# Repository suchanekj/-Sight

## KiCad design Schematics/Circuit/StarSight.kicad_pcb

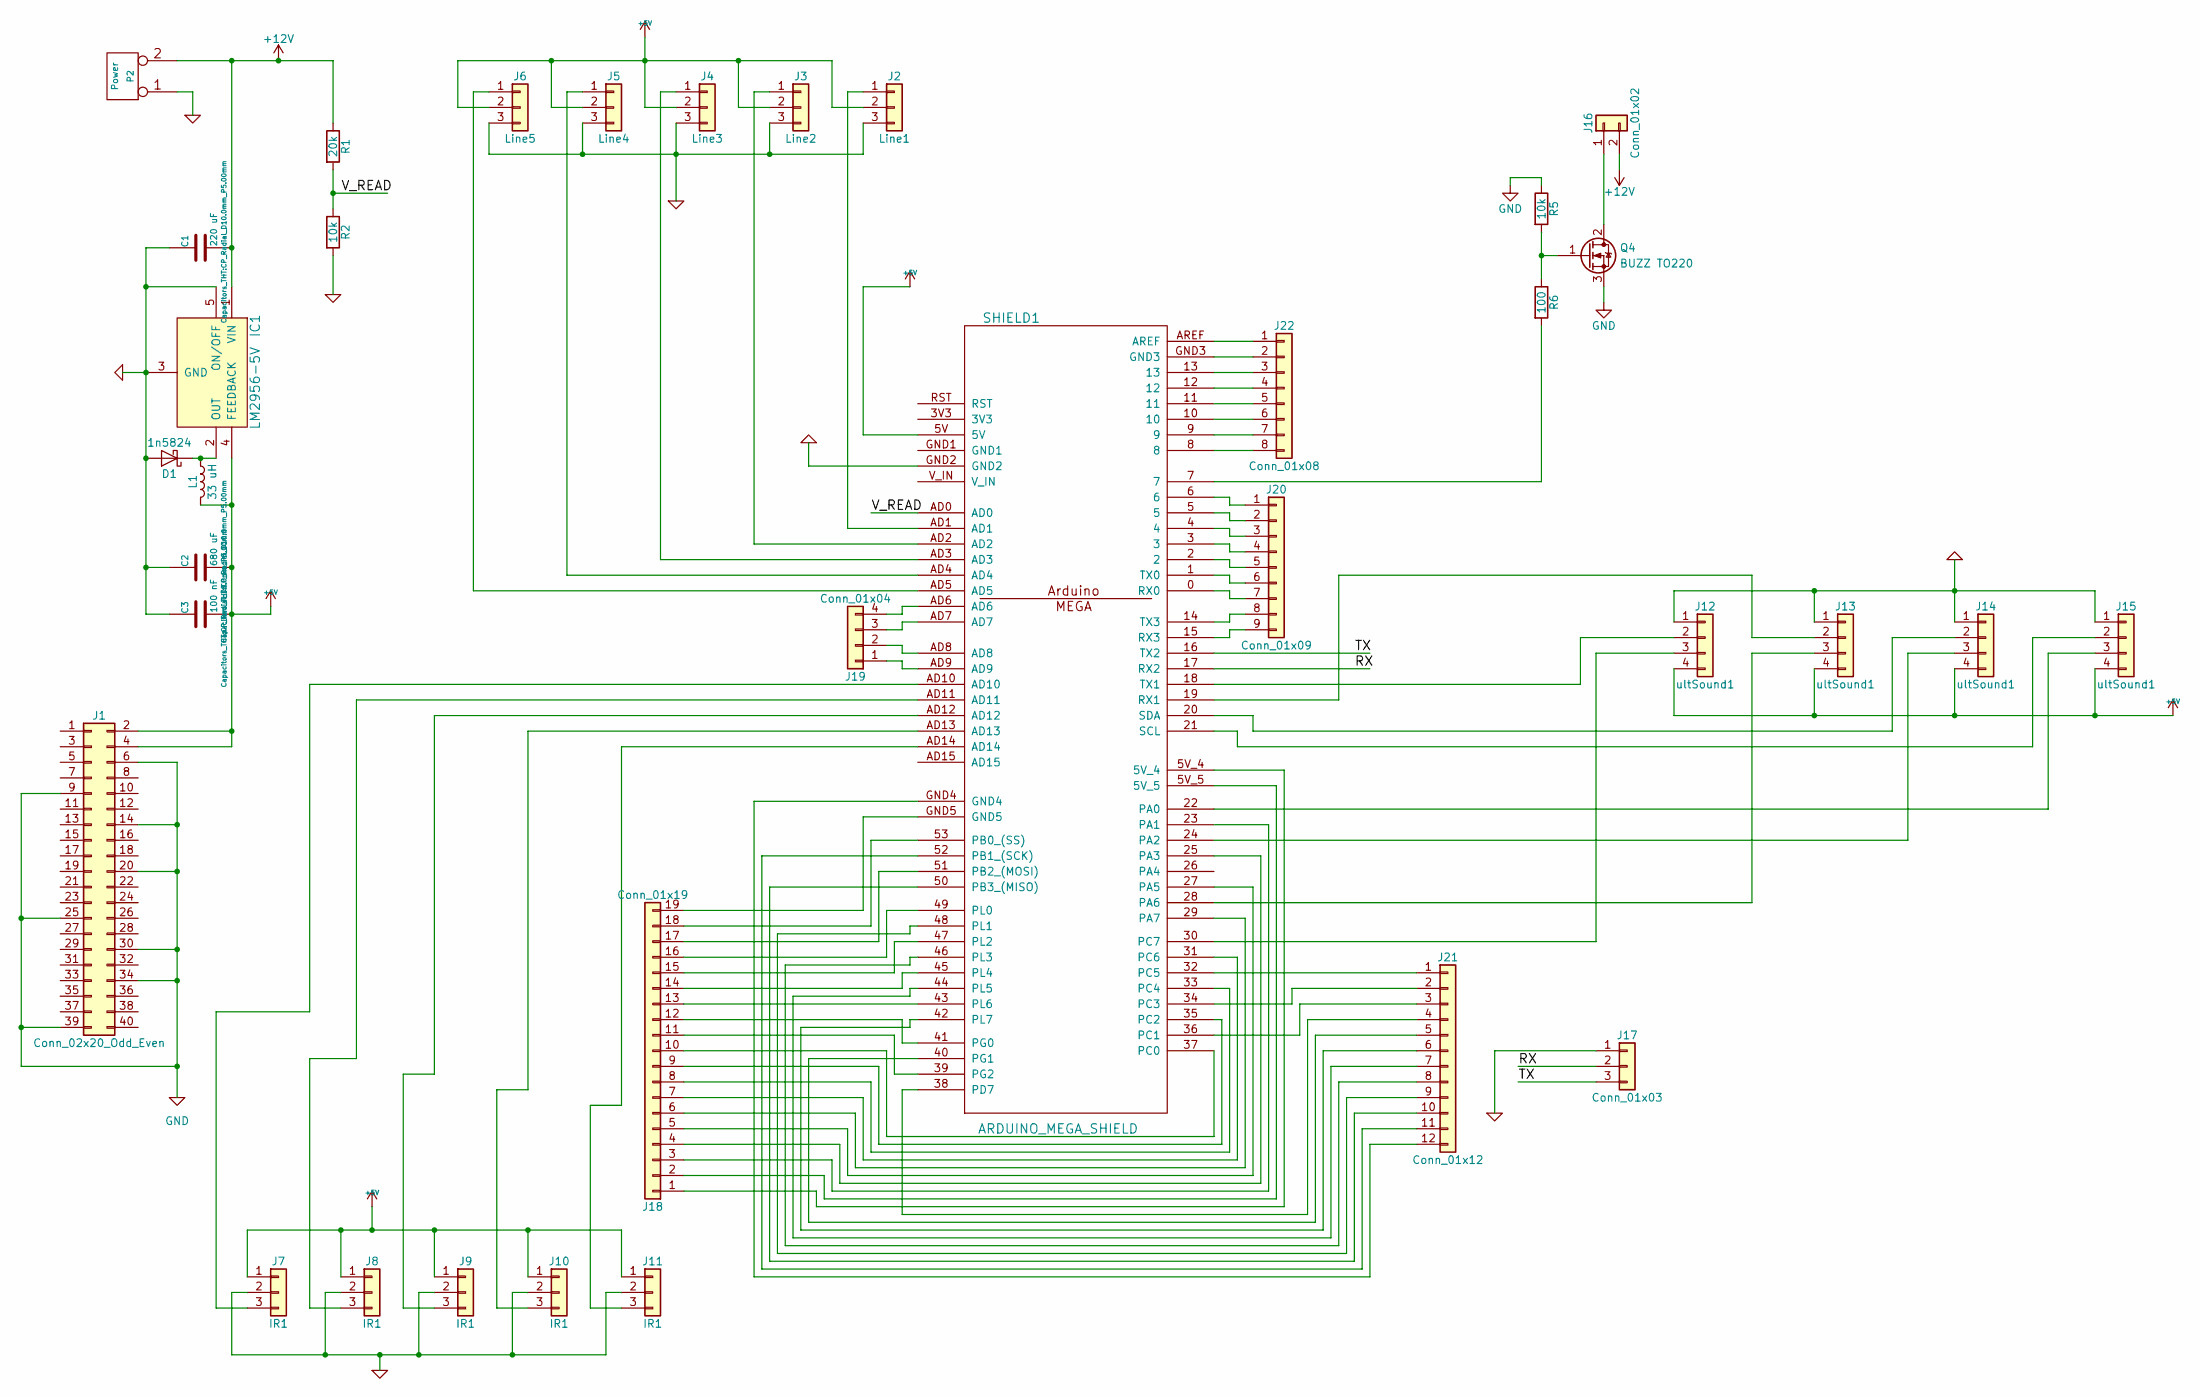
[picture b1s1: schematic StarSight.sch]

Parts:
C1: 220 uF; CP_Radial_D10.0mm_P5.00mm
C2: 680 uF; CP_Radial_D10.0mm_P5.00mm
C3: 100 nF; CP_Radial_D8.0mm_P5.00mm
D1: 1n5824; D_DO-201_P15.24mm_Horizontal
IC1: LM2956-5V; TO170P470X1016X2092-5P
J1: Conn_02x20_Odd_Even; Pin_Header_Straight_2x20_Pitch2.54mm
J2: Line1; Pin_Header_Straight_1x03_Pitch2.54mm
J3: Line2; Pin_Header_Straight_1x03_Pitch2.54mm
J4: Line3; Pin_Header_Straight_1x03_Pitch2.54mm
J5: Line4; Pin_Header_Straight_1x03_Pitch2.54mm
J6: Line5; Pin_Header_Straight_1x03_Pitch2.54mm
J7, J8, J9, J10, J11: IR1; Pin_Header_Straight_1x03_Pitch2.54mm
J12, J13, J14, J15: ultSound1; Pin_Header_Straight_1x04_Pitch2.54mm
J16: Conn_01x02; TerminalBlock_Philmore_TB132_02x5mm_Straight
J17: Conn_01x03; Pin_Header_Straight_1x03_Pitch2.54mm
J18: Conn_01x19; Pin_Header_Straight_1x19_Pitch2.54mm
J19: Conn_01x04; Pin_Header_Straight_1x04_Pitch2.54mm
J20: Conn_01x09; Pin_Header_Straight_1x09_Pitch2.54mm
J21: Conn_01x12; Pin_Header_Straight_1x12_Pitch2.54mm
J22: Conn_01x08; Pin_Header_Straight_1x08_Pitch2.54mm
L1: 33 uH; L_Toroid_Vertical_L16.0mm_W8.0mm_P7.62mm
P2: Power; TerminalBlock_Philmore_TB132_02x5mm_Straight
Q4: BUZZ TO220; Pin_Header_Straight_1x03_Pitch2.54mm
R1: 20k; R_Axial_DIN0309_L9.0mm_D3.2mm_P12.70mm_Horizontal
R2, R5: 10k; R_Axial_DIN0309_L9.0mm_D3.2mm_P12.70mm_Horizontal
R6: 100; R_Axial_DIN0309_L9.0mm_D3.2mm_P12.70mm_Horizontal
SHIELD1: ARDUINO_MEGA_SHIELD

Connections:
+5V: C2.2, C3.2, IC1.4 (FEEDBACK), J1.2, J1.4, J2.2, J3.2, J4.2, J5.2, J6.2, J7.1, J8.1, J9.1, J10.1, J11.1, J12.4, J13.4, J14.4, J15.4, L1.2, SHIELD1.5V
+12V: C1.2, IC1.1 (VIN), J16.2, P2.2 (PM), R1.1; also elsewhere on the board
/RX: J17.2, SHIELD1.17 (RX2)
/TX: J17.3, SHIELD1.16 (TX2)
/V_READ: R1.2, R2.1, SHIELD1.AD0
GND: C1.1, C2.1, C3.1, D1.2 (A), IC1.3 (GND), IC1.5 (ON/OFF), J1.6, J1.9, J1.14, J1.20, J1.25, J1.30, J1.34, J1.39, J2.3, J3.3, J4.3, J5.3, J6.3, J7.2, J8.2, J9.2, J10.2, J11.2, J12.1, J13.1, J14.1, J15.1, J17.1, P2.1, Q4.3 (S), R2.2, R5.1, SHIELD1.GND2
unnamed: D1.1 (K), IC1.2 (OUT), L1.1
unnamed 7: J16.1, Q4.2 (D); also elsewhere on the board
unnamed 8: J1.1; also elsewhere on the board
unnamed 9: J1.3; also elsewhere on the board
unnamed 10: J1.5; also elsewhere on the board
unnamed 11: J1.7; also elsewhere on the board
unnamed 12: J1.8; also elsewhere on the board
unnamed 13: J1.10; also elsewhere on the board
unnamed 14: J1.11; also elsewhere on the board
unnamed 15: J1.12; also elsewhere on the board
unnamed 16: J1.13; also elsewhere on the board
unnamed 17: J1.15; also elsewhere on the board
unnamed 18: J1.16; also elsewhere on the board
unnamed 19: J1.17; also elsewhere on the board
unnamed 20: J1.18; also elsewhere on the board
unnamed 21: J1.19; also elsewhere on the board
unnamed 22: J1.21; also elsewhere on the board
unnamed 23: J1.22; also elsewhere on the board
unnamed 24: J1.23; also elsewhere on the board
unnamed 25: J1.24; also elsewhere on the board
unnamed 26: J1.26; also elsewhere on the board
unnamed 27: J1.27; also elsewhere on the board
unnamed 28: J1.28; also elsewhere on the board
unnamed 29: J1.29; also elsewhere on the board
unnamed 30: J1.31; also elsewhere on the board
unnamed 31: J1.32; also elsewhere on the board
unnamed 32: J1.33; also elsewhere on the board
unnamed 33: J1.35; also elsewhere on the board
unnamed 34: J1.36; also elsewhere on the board
unnamed 35: J1.37; also elsewhere on the board
unnamed 36: J1.38; also elsewhere on the board
unnamed 37: J1.40; also elsewhere on the board
unnamed: J2.1, SHIELD1.AD1
unnamed: J3.1, SHIELD1.AD2
unnamed: J4.1, SHIELD1.AD3
unnamed: J5.1, SHIELD1.AD4
unnamed: J6.1, SHIELD1.AD5
unnamed: J7.3, SHIELD1.AD10
unnamed: J8.3, SHIELD1.AD11
unnamed: J9.3, SHIELD1.AD12
unnamed: J10.3, SHIELD1.AD13
unnamed: J11.3, SHIELD1.AD14
unnamed: J12.2, SHIELD1.18 (TX1)
unnamed: J12.3, SHIELD1.30 (PC7)
unnamed: J13.2, SHIELD1.19 (RX1)
unnamed: J13.3, SHIELD1.28 (PA6)
unnamed: J14.2, SHIELD1.20 (SDA)
unnamed: J14.3, SHIELD1.24 (PA2)
unnamed: J15.2, SHIELD1.21 (SCL)
unnamed: J15.3, SHIELD1.22 (PA0)
unnamed: J18.1, SHIELD1.5V_4
unnamed: J18.2, SHIELD1.5V_5
unnamed: J18.3, SHIELD1.23 (PA1)
unnamed: J18.4, SHIELD1.25 (PA3)
unnamed: J18.5, SHIELD1.27 (PA5)
unnamed: J18.6, SHIELD1.29 (PA7)
unnamed: J18.7, SHIELD1.31 (PC6)
unnamed: J18.8, SHIELD1.33 (PC4)
unnamed: J18.9, SHIELD1.35 (PC2)
unnamed: J18.10, SHIELD1.37 (PC0)
unnamed: J18.11, SHIELD1.39 (PG2)
unnamed: J18.12, SHIELD1.41 (PG0)
unnamed: J18.13, SHIELD1.43 (PL6)
unnamed: J18.14, SHIELD1.45 (PL4)
unnamed: J18.15, SHIELD1.47 (PL2)
unnamed: J18.16, SHIELD1.49 (PL0)
unnamed: J18.17, SHIELD1.51 (PB2_(MOSI))
unnamed: J18.18, SHIELD1.53 (PB0_(SS))
unnamed: J18.19, SHIELD1.GND5
unnamed: J19.1, SHIELD1.AD9
unnamed: J19.2, SHIELD1.AD8
unnamed: J19.3, SHIELD1.AD7
unnamed: J19.4, SHIELD1.AD6
unnamed: J20.1, SHIELD1.6
unnamed: J20.2, SHIELD1.5
unnamed: J20.3, SHIELD1.4
unnamed: J20.4, SHIELD1.3
unnamed: J20.5, SHIELD1.2
unnamed: J20.6, SHIELD1.1 (TX0)
unnamed: J20.7, SHIELD1.0 (RX0)
unnamed: J20.8, SHIELD1.14 (TX3)
unnamed: J20.9, SHIELD1.15 (RX3)
unnamed: J21.1, SHIELD1.32 (PC5)
unnamed: J21.2, SHIELD1.34 (PC3)
unnamed: J21.3, SHIELD1.36 (PC1)
unnamed: J21.4, SHIELD1.38 (PD7)
unnamed: J21.5, SHIELD1.40 (PG1)
unnamed: J21.6, SHIELD1.42 (PL7)
unnamed: J21.7, SHIELD1.44 (PL5)
unnamed: J21.8, SHIELD1.46 (PL3)
unnamed: J21.9, SHIELD1.48 (PL1)
unnamed: J21.10, SHIELD1.50 (PB3_(MISO))
unnamed: J21.11, SHIELD1.52 (PB1_(SCK))
unnamed: J21.12, SHIELD1.GND4
unnamed: J22.1, SHIELD1.AREF
unnamed: J22.2, SHIELD1.GND3
unnamed: J22.3, SHIELD1.13
unnamed: J22.4, SHIELD1.12
unnamed: J22.5, SHIELD1.11
unnamed: J22.6, SHIELD1.10
unnamed: J22.7, SHIELD1.9
unnamed: J22.8, SHIELD1.8
unnamed: Q4.1 (G), R5.2, R6.1
unnamed: R6.2, SHIELD1.7

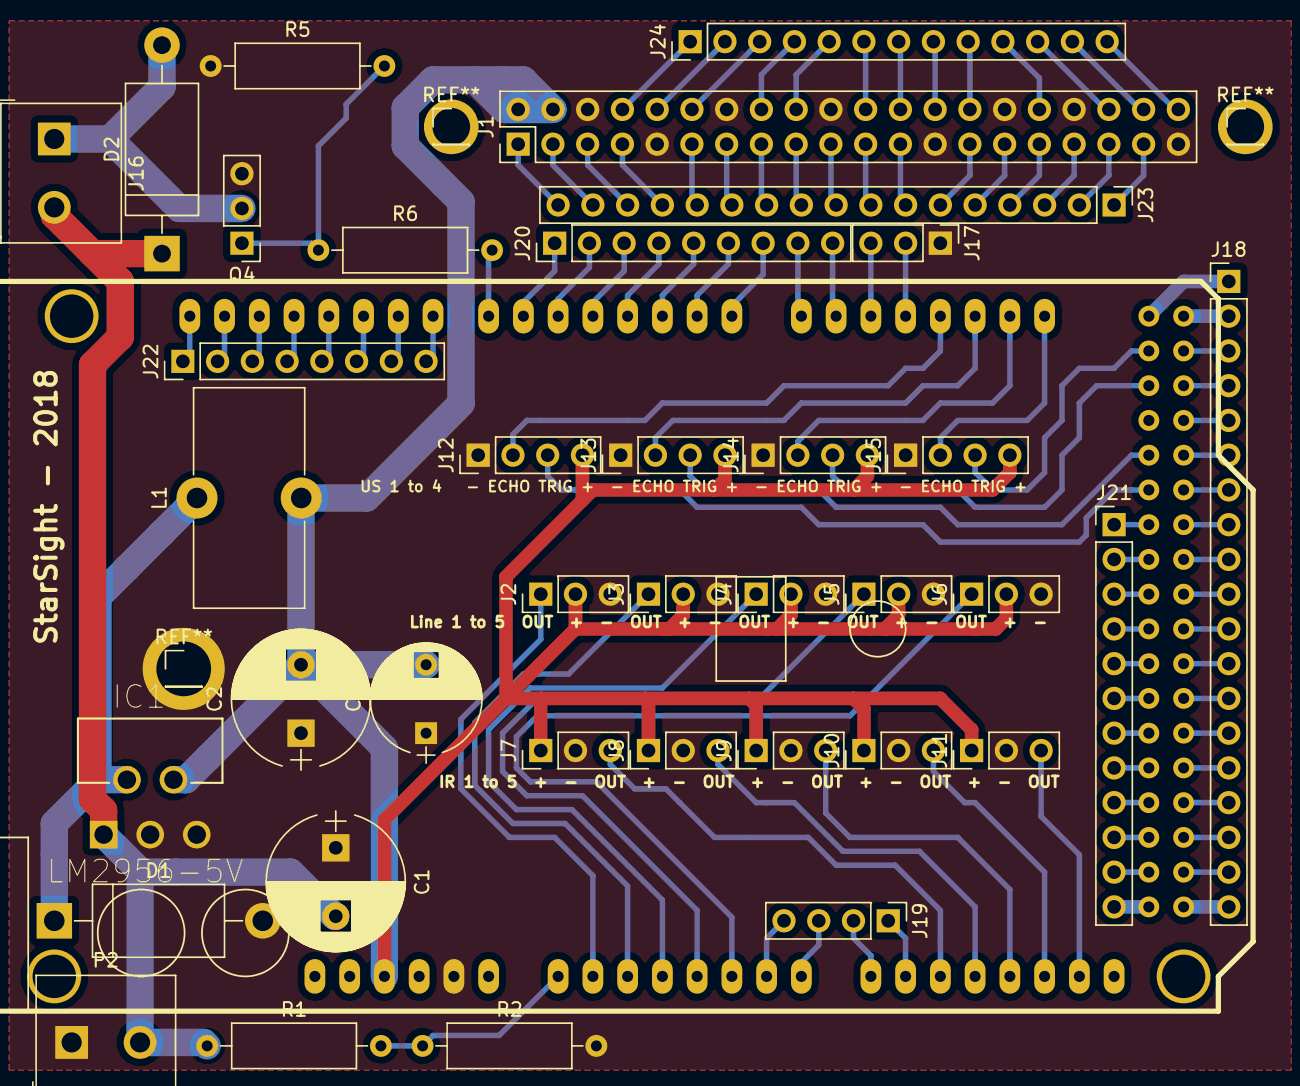
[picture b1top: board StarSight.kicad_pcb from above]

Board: 2 copper layers, 38 parts (0 on the bottom side), 110 nets.

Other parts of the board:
D2: D; D_DO-201_P15.24mm_Horizontal
J23: Conn_01x17; Pin_Header_Straight_1x17_Pitch2.54mm
J24: Conn_01x13; Pin_Header_Straight_1x13_Pitch2.54mm

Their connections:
+12V: D2.1; also elsewhere on the board
unnamed 7: D2.2; also elsewhere on the board
unnamed 8: J23.17; also elsewhere on the board
unnamed 9: J23.16; also elsewhere on the board
unnamed 10: J23.15; also elsewhere on the board
unnamed 11: J23.14; also elsewhere on the board
unnamed 12: J24.1; also elsewhere on the board
unnamed 13: J24.2; also elsewhere on the board
unnamed 14: J23.13; also elsewhere on the board
unnamed 15: J24.3; also elsewhere on the board
unnamed 16: J23.12; also elsewhere on the board
unnamed 17: J23.11; also elsewhere on the board
unnamed 18: J24.4; also elsewhere on the board
unnamed 19: J23.10; also elsewhere on the board
unnamed 20: J24.5; also elsewhere on the board
unnamed 21: J23.9; also elsewhere on the board
unnamed 22: J23.8; also elsewhere on the board
unnamed 23: J24.6; also elsewhere on the board
unnamed 24: J23.7; also elsewhere on the board
unnamed 25: J24.7; also elsewhere on the board
unnamed 26: J24.8; also elsewhere on the board
unnamed 27: J23.6; also elsewhere on the board
unnamed 28: J24.9; also elsewhere on the board
unnamed 29: J23.5; also elsewhere on the board
unnamed 30: J23.4; also elsewhere on the board
unnamed 31: J24.10; also elsewhere on the board
unnamed 32: J23.3; also elsewhere on the board
unnamed 33: J23.2; also elsewhere on the board
unnamed 34: J24.11; also elsewhere on the board
unnamed 35: J23.1; also elsewhere on the board
unnamed 36: J24.12; also elsewhere on the board
unnamed 37: J24.13; also elsewhere on the board

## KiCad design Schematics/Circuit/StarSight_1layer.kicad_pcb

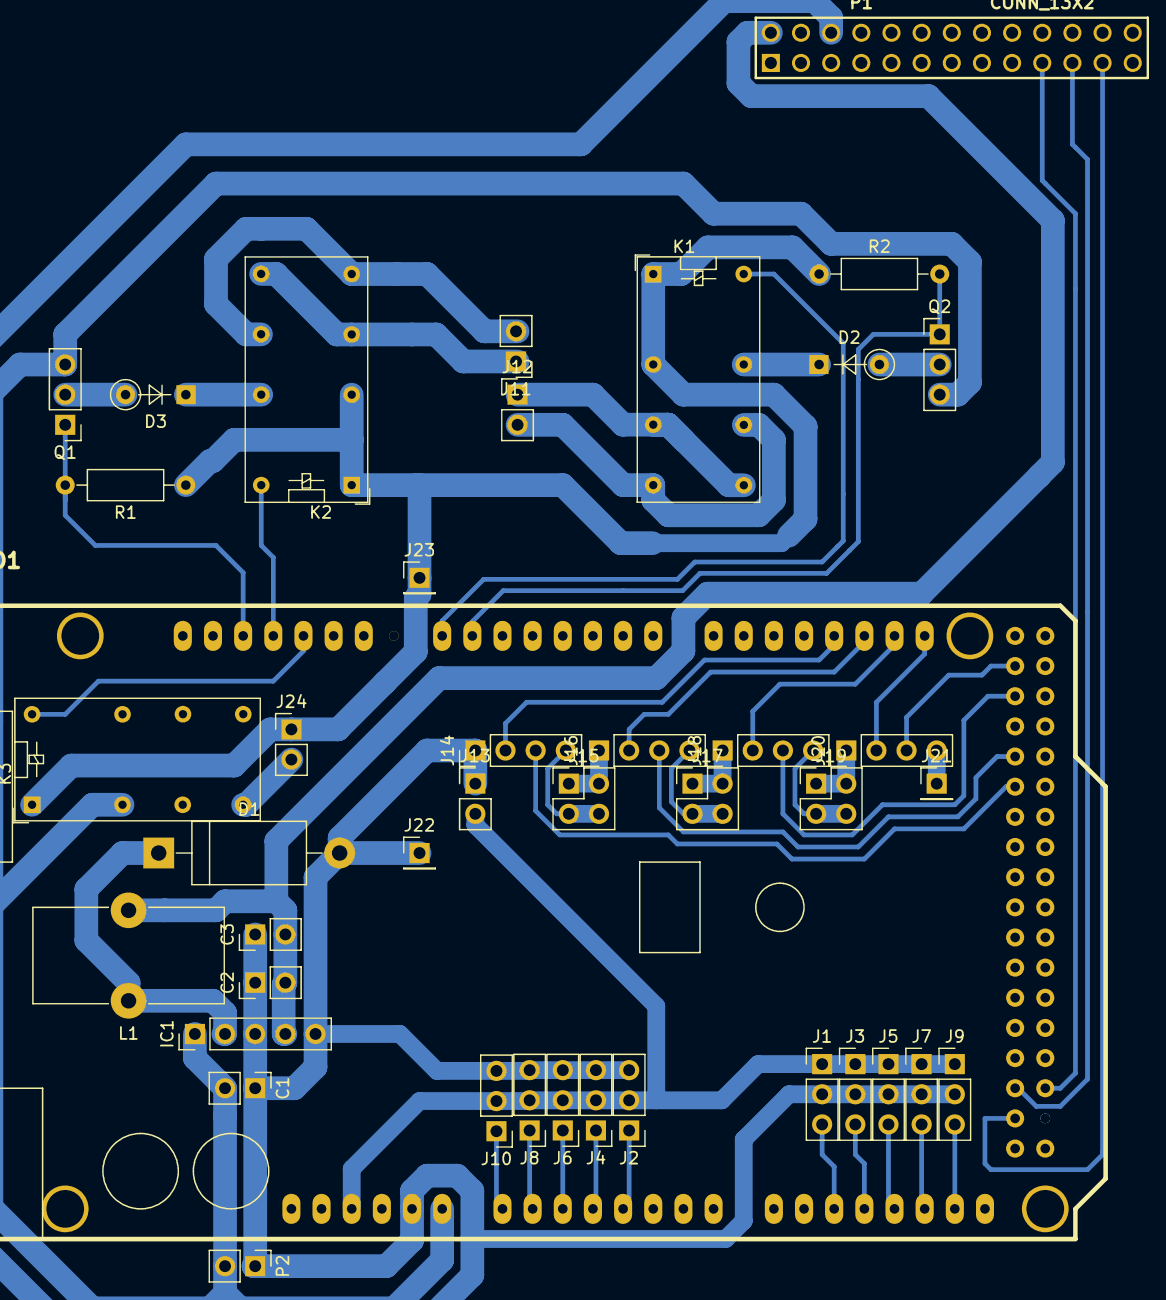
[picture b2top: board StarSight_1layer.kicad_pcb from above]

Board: 2 copper layers, 42 parts (0 on the bottom side), 48 nets.

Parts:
C1, C2: 10 uF; Pin_Header_Straight_1x02_Pitch2.54mm
C3: 100 nF; Pin_Header_Straight_1x02_Pitch2.54mm
D1: 1n5824; D_DO-201_P15.24mm_Horizontal
D2, D3: D; D_DO-35_SOD27_P5.08mm_Vertical_KathodeUp
IC1: LM2956-5V; Pin_Header_Straight_1x05_Pitch2.54mm
J1, J3, J5, J7, J9: IR1; Pin_Header_Straight_1x03_Pitch2.54mm
J2: Line5; Pin_Header_Straight_1x03_Pitch2.54mm
J4: Line4; Pin_Header_Straight_1x03_Pitch2.54mm
J6: Line3; Pin_Header_Straight_1x03_Pitch2.54mm
J8: Line2; Pin_Header_Straight_1x03_Pitch2.54mm
J10: Line1; Pin_Header_Straight_1x03_Pitch2.54mm
J11, J12, J13, J24: Conn_01x02; Pin_Header_Straight_1x02_Pitch2.54mm
J14, J16, J18, J20: ultSound1; Pin_Header_Straight_1x04_Pitch2.54mm
J15, J17, J19: Conn_02x02_Counter_Clockwise; Pin_Header_Straight_2x02_Pitch2.54mm
J21, J22, J23: Conn_01x01; Pin_Header_Straight_1x01_Pitch2.54mm
K1, K2, K3: RELAY; Relay_DPDT_Omron_G5V-2
L1: 33 uH; L_Toroid_Vertical_L16.0mm_W8.0mm_P7.62mm
P1: CONN_13X2; pin_array_13x2
P2: Power; Pin_Header_Straight_1x02_Pitch2.54mm
Q1, Q2: Q_NMOS_GDS; Pin_Header_Straight_1x03_Pitch2.54mm
R1, R2: 10k; R_Axial_DIN0207_L6.3mm_D2.5mm_P10.16mm_Horizontal
SHIELD1: ARDUINO_MEGA_SHIELD

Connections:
+5V: J1.1, J2.2, J3.1, J4.2, J5.1, J6.2, J7.1, J8.2, J9.1, J10.2, J13.2, SHIELD1.5V
+12V: C1.2, IC1.1, K3.4, P2.2, Q1.3, Q2.3, SHIELD1.V_IN
/GPIO9(MISO): P1.21, SHIELD1.50
/GPIO10(MOSI): P1.19, SHIELD1.51
/GPIO11(SCLK): P1.23, SHIELD1.52
GND: C1.1, C2.1, C3.1, D1.2, IC1.3, IC1.5, J1.2, J2.3, J3.2, J4.3, J5.2, J6.3, J7.2, J8.3, J9.2, J10.3, J13.1, J14.1, J22.1, P1.6, P2.1, SHIELD1.GND2
unnamed: C2.2, C3.2, IC1.4, L1.2, P1.2
unnamed: D1.1, IC1.2, L1.1
unnamed: D2.1, K1.13
unnamed: D2.2, Q2.2
unnamed: D3.1, K2.13
unnamed: D3.2, Q1.2
unnamed: J1.3, SHIELD1.AD10
unnamed: J2.1, SHIELD1.AD4
unnamed: J3.3, SHIELD1.AD11
unnamed: J4.1, SHIELD1.AD3
unnamed: J5.3, SHIELD1.AD12
unnamed: J6.1, SHIELD1.AD2
unnamed: J7.3, SHIELD1.AD13
unnamed: J8.1, SHIELD1.AD1
unnamed: J9.3, SHIELD1.AD14
unnamed: J10.1, SHIELD1.AD0
unnamed: J11.1, K2.6, K2.9
unnamed: J11.2, K2.8, K2.11
unnamed: J12.1, K1.6, K1.9
unnamed: J12.2, K1.8, K1.11
unnamed: J14.2, SHIELD1.18
unnamed: J14.3, SHIELD1.30
unnamed: J14.4, J15.3, J15.4
unnamed: J15.1, J15.2, J16.1
unnamed: J16.2, SHIELD1.19
unnamed: J16.3, SHIELD1.28
unnamed: J16.4, J17.3, J17.4
unnamed: J17.1, J17.2, J18.1
unnamed: J18.2, SHIELD1.20
unnamed: J18.3, SHIELD1.24
unnamed: J18.4, J19.3, J19.4
unnamed: J19.1, J19.2, J20.1
unnamed: J20.2, SHIELD1.21
unnamed: J20.3, SHIELD1.22
unnamed: J20.4, J21.1
unnamed: J23.1, J24.1, K1.1, K1.4, K2.1, K2.4, K3.1, R1.1, R2.1
unnamed: J24.2, K3.8
unnamed: K1.16, SHIELD1.7
unnamed: K2.16, SHIELD1.12
unnamed: K3.16, SHIELD1.11
unnamed: Q1.1, R1.2, SHIELD1.13
unnamed: Q2.1, R2.2, SHIELD1.6

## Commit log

2017-12-17 Add last year code and schematic base
2017-12-23 Add the rest of the schematic
2017-12-24 Add pcb layout
2017-12-25 Fix pcb
2017-12-29 Edit pcb
2017-12-29 Add switched regulator and motors
2017-12-29 Fix footprint missing
2017-12-30 Fix pcb power suply and motors
2018-01-21 Add single sided version of the circuit
2018-01-22 Add model
2018-02-04 Add sensor placeholders
2018-02-12 Change inductor footprint
2018-02-12 Add fan
2018-02-12 Edit fan relay
2018-02-19 Reroute main circuit board to fit 1 dm^2
2018-02-19 Fix relays and board size
2018-02-20 Added MonoVision Odometry
2018-02-20 Edit board thickness in the model
2018-02-20 Merge branch 'master' of https://github.com/suchanekj/StarSight
    # Please enter a commit message to explain why this merge is necessary,
    # especially if it merges an updated upstream into a topic branch.
    #
    # Lines starting with '#' will be ignored, and an empty message aborts
    # the commit.
2018-02-22 Export schematics and board
2018-02-23 fix IR base
2018-02-25 Edit board - remove drivers, add pins
2018-02-25 Edit circuit exports
2018-02-25 Edit robot model and add exports for laser
2018-02-25 Add pins for raspberry and few circuit fixes
2018-03-03 Added RoboModel with
2018-03-03 Added RoboModel arduino input
2018-03-04 Added RoboClaw basics
2018-03-04 Add new arduino code
2018-03-06 Add forgotten arduino files
2018-03-07 Add battery voltage reading
2018-03-07 Add new driver board
2018-03-07 Added go test
2018-03-07 Fixed go test
2018-03-07 Testing funs
2018-03-07 Add led signal
2018-03-08 Testing sensors with motors
2018-03-08 Upgraded go function
2018-03-08 Fixed Go
2018-03-08 Edit communication
2018-03-08 add better go
2018-03-08 Hotfixes
2018-03-08 fix go
2018-03-08 Add breaking
